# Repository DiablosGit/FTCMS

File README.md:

This is an attempt to build an easy to use BMS on easy to use Hardware. Everyone contributing to this project is welcome.

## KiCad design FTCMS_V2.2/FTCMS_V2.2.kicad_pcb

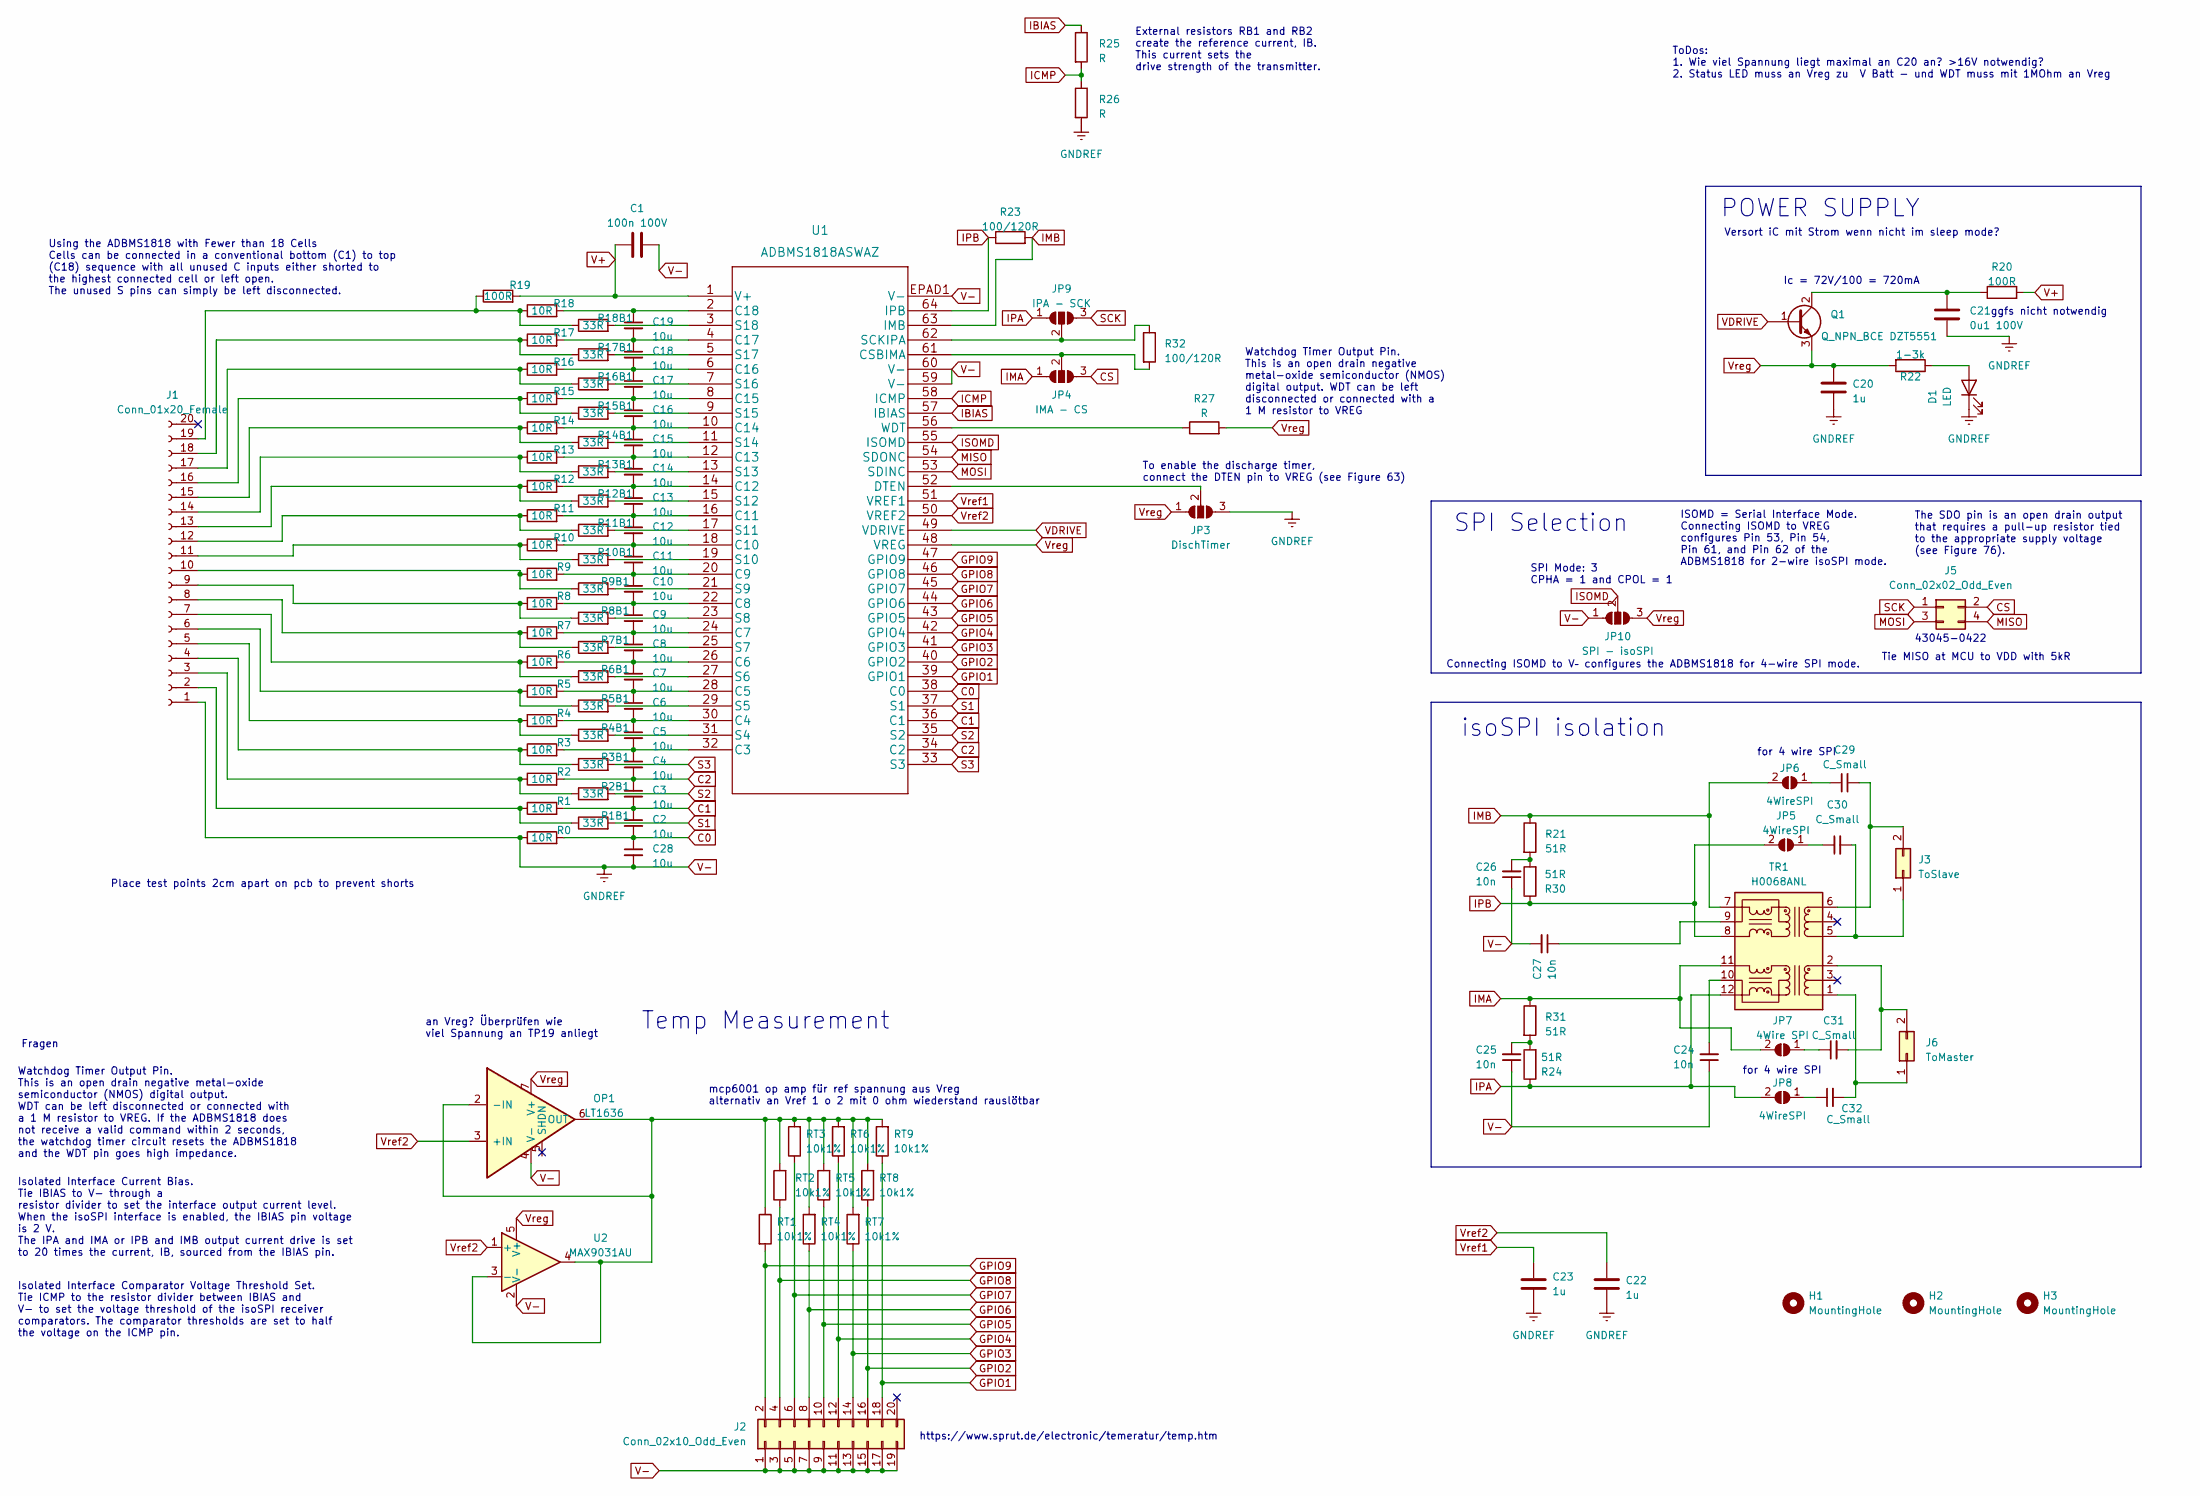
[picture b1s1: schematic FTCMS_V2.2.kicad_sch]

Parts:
C1: 100n 100V; C_1206_3216Metric_Pad1.33x1.80mm_HandSolder
C2, C3, C4, C5, C6, C7, C8, C9, C10, C11, C12, C13, C14, C15, C16, C17, C18, C19, C28: 10u; C_0603_1608Metric_Pad1.08x0.95mm_HandSolder
C20, C22, C23: 1u; C_1206_3216Metric_Pad1.33x1.80mm_HandSolder
C21: 0u1 100V; C_1206_3216Metric_Pad1.33x1.80mm_HandSolder
C24, C25, C26, C27: 10n; C_1206_3216Metric_Pad1.33x1.80mm_HandSolder
C29, C30, C31, C32: C_Small; C_1206_3216Metric_Pad1.33x1.80mm_HandSolder
D1: LED; LED_1206_3216Metric_Pad1.42x1.75mm_HandSolder
H1, H2, H3: MountingHole; MountingHole_3.2mm_M3_DIN965
J1: Conn_01x20_Female; PinSocket_2x10_P2.54mm_Vertical
J2: Conn_02x10_Odd_Even; PinSocket_2x10_P2.54mm_Vertical
J3: ToSlave; Molex_Micro-Fit_3.0_43650-0200_1x02_P3.00mm_Horizontal
J5: Conn_02x02_Odd_Even; Molex_Micro-Fit_3.0_43045-0400_2x02_P3.00mm_Horizontal
J6: ToMaster; Molex_Micro-Fit_3.0_43650-0200_1x02_P3.00mm_Horizontal
JP3: DischTimer; SolderJumper-3_P2.0mm_Open_TrianglePad1.0x1.5mm
JP4: IMA - CS; SolderJumper-3_P2.0mm_Open_TrianglePad1.0x1.5mm
JP5, JP6, JP8: 4WireSPI; SolderJumper-2_P1.3mm_Open_TrianglePad1.0x1.5mm
JP7: 4Wire SPI; SolderJumper-2_P1.3mm_Open_TrianglePad1.0x1.5mm
JP9: IPA - SCK; SolderJumper-3_P2.0mm_Open_TrianglePad1.0x1.5mm
JP10: SPI - isoSPI; SolderJumper-3_P2.0mm_Open_TrianglePad1.0x1.5mm
OP1: LT1636; DIP-8_W7.62mm_Socket_LongPads
Q1: Q_NPN_BCE DZT5551; SOT-223-3_TabPin2
R0, R1, R2, R3, R4, R5, R6, R7, R8, R9, R10, R11, R12, R13, R14, R15, R16, R17, R18: 10R; R_1206_3216Metric_Pad1.30x1.75mm_HandSolder
R1B1, R2B1, R3B1, R4B1, R5B1, R6B1, R7B1, R8B1, R9B1, R10B1, R11B1, R12B1, R13B1, R14B1, R15B1, R16B1, R17B1, R18B1: 33R; R_1206_3216Metric_Pad1.30x1.75mm_HandSolder
R19, R20: 100R; R_1206_3216Metric_Pad1.30x1.75mm_HandSolder
R21, R24, R30, R31: 51R; R_1206_3216Metric_Pad1.30x1.75mm_HandSolder
R22: 1-3k; R_1206_3216Metric_Pad1.30x1.75mm_HandSolder
R23, R32: 100/120R; R_1206_3216Metric_Pad1.30x1.75mm_HandSolder
R25, R26, R27: R; R_1206_3216Metric_Pad1.30x1.75mm_HandSolder
RT1, RT2, RT3, RT4, RT5, RT6, RT7, RT8, RT9: 10k1%; R_1206_3216Metric_Pad1.30x1.75mm_HandSolder
TR1: H0068ANL
U1: ADBMS1818ASWAZ; LQFP-64-1EP_10x10mm_P0.5mm_EP5x5mm_ThermalVias
U2: MAX9031AU; SOT-23-5

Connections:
C0: C2.2, C28.1, R0.2, U1.38 (C0)
C1: C2.1, C3.2, R1.2, U1.36 (C1)
C2: C3.1, C4.2, R2.2, U1.34 (C2)
CS: J5.2, JP4.3 (B)
GPIO1: J2.18, RT9.1, U1.39 (GPIO1)
GPIO2: J2.16, RT8.1, U1.40 (GPIO2)
GPIO3: J2.14, RT7.1, U1.41 (GPIO3)
GPIO4: J2.12, RT6.1, U1.42 (GPIO4)
GPIO5: J2.10, RT5.1, U1.43 (GPIO5)
GPIO6: J2.8, RT4.1, U1.44 (GPIO6)
GPIO7: J2.6, RT3.1, U1.45 (GPIO7)
GPIO8: J2.4, RT2.1, U1.46 (GPIO8)
GPIO9: J2.2, RT1.2, U1.47 (GPIO9)
IBIAS: R25.1, U1.57 (IBIAS)
ICMP: R25.2, R26.1, U1.58 (ICMP)
IMA: JP4.1 (A), JP7.2 (B), R31.1, TR1.11 (RX-)
IMB: JP6.2 (B), R21.1, R23.2, TR1.7 (TX-), U1.63 (IMB)
IPA: JP8.2 (B), JP9.1 (A), R24.1, TR1.12 (RX+)
IPB: JP5.2 (B), R23.1, R30.1, TR1.8 (TX+), U1.64 (IPB)
ISOMD: JP10.2 (C), U1.55 (ISOMD)
MISO: J5.4, U1.54 (SDONC)
MOSI: J5.3, U1.53 (SDINC)
unnamed: C25.2, R24.2, R31.2
unnamed: C26.2, R21.2, R30.2
unnamed: D1.2 (A), R22.1
unnamed: J1.2, R1.1, R1B1.1
unnamed: J1.3, R2.1, R2B1.1
unnamed: J1.4, R3.1, R3B1.1
unnamed: J1.5, R4.1, R4B1.1
unnamed: J1.6, R5.1, R5B1.1
unnamed: J1.7, R6.1, R6B1.1
unnamed: J1.8, R7.1, R7B1.1
unnamed: J1.9, R8.1, R8B1.1
unnamed: J1.10, R9.1, R9B1.1
unnamed: J1.11, R10.1, R10B1.1
unnamed: J1.12, R11.1, R11B1.1
unnamed: J1.13, R12.1, R12B1.1
unnamed: J1.14, R13.1, R13B1.1
unnamed: J1.15, R14.1, R14B1.1
unnamed: J1.16, R15.1, R15B1.1
unnamed: J1.17, R16.1, R16B1.1
unnamed: J1.18, R17.1, R17B1.1
unnamed: J1.19, R18.1, R18B1.1, R19.1
unnamed: C30.2, J3.1, TR1.5 (TD+)
unnamed: C29.2, J3.2, TR1.6 (TD-)
unnamed: C32.2, J6.1, TR1.1 (RD+)
unnamed: C31.2, J6.2, TR1.2 (RD-)
unnamed: JP3.2 (C), U1.52 (DTEN)
unnamed: JP4.2 (C), R32.2, U1.61 (CSBIMA)
unnamed: C30.1, JP5.1 (A)
unnamed: C29.1, JP6.1 (A)
unnamed: C31.1, JP7.1 (A)
unnamed: C32.1, JP8.1 (A)
unnamed: JP9.2 (C), R32.1, U1.62 (SCKIPA)
unnamed: OP1.2 (-IN), OP1.6 (OUT), RT1.1, RT2.2, RT3.2, RT4.2, RT5.2, RT6.2, RT7.2, RT8.2, RT9.2, U2.3 (-), U2.4
unnamed: C21.1, Q1.2 (C), R20.1
unnamed: C24.2, TR1.10 (RXCT)
unnamed: C27.1, TR1.9 (TXCT)
unnamed: C4.1, C5.2, R3.2, U1.32 (C3)
unnamed: C5.1, C6.2, R4.2, U1.30 (C4)
unnamed: C6.1, C7.2, R5.2, U1.28 (C5)
unnamed: C7.1, C8.2, R6.2, U1.26 (C6)
unnamed: C8.1, C9.2, R7.2, U1.24 (C7)
unnamed: C9.1, C10.2, R8.2, U1.22 (C8)
unnamed: C10.1, C11.2, R9.2, U1.20 (C9)
unnamed: C11.1, C12.2, R10.2, U1.18 (C10)
unnamed: C12.1, C13.2, R11.2, U1.16 (C11)
unnamed: C13.1, C14.2, R12.2, U1.14 (C12)
unnamed: C14.1, C15.2, R13.2, U1.12 (C13)
unnamed: C15.1, C16.2, R14.2, U1.10 (C14)
unnamed: C16.1, C17.2, R15.2, U1.8 (C15)
unnamed: C17.1, C18.2, R16.2, U1.6 (C16)
unnamed: C18.1, C19.2, R17.2, U1.4 (C17)
unnamed: C19.1, R18.2, U1.2 (C18)
unnamed: R4B1.2, U1.31 (S4)
unnamed: R5B1.2, U1.29 (S5)
unnamed: R6B1.2, U1.27 (S6)
unnamed: R7B1.2, U1.25 (S7)
unnamed: R8B1.2, U1.23 (S8)
unnamed: R9B1.2, U1.21 (S9)
unnamed: R10B1.2, U1.19 (S10)
unnamed: R11B1.2, U1.17 (S11)
unnamed: R12B1.2, U1.15 (S12)
unnamed: R13B1.2, U1.13 (S13)
unnamed: R14B1.2, U1.11 (S14)
unnamed: R15B1.2, U1.9 (S15)
unnamed: R16B1.2, U1.7 (S16)
unnamed: R17B1.2, U1.5 (S17)
unnamed: R18B1.2, U1.3 (S18)
unnamed: R27.1, U1.56 (WDT)
S1: R1B1.2, U1.37 (S1)
S2: R2B1.2, U1.35 (S2)
S3: R3B1.2, U1.33 (S3)
SCK: J5.1, JP9.3 (B)
V+: C1.1, R19.2, R20.2, U1.1 (V+)
V-: C1.2, C20.2, C21.2, C22.2, C23.2, C24.1, C25.1, C26.1, C27.2, C28.2, D1.1 (K), J1.1, J2.1, J2.3, J2.5, J2.7, J2.9, J2.11, J2.13, J2.15, J2.17, J2.19, JP3.3 (B), JP10.1 (A), R0.1, R26.2, U1.59 (V-), U1.60 (V-), U1.EPAD1 (V-), U2.2 (V-)
VDRIVE: Q1.1 (B), U1.49 (VDRIVE)
Vref1: C23.1, U1.51 (VREF1)
Vref2: C22.1, U1.50 (VREF2), U2.1 (+)
Vreg: C20.1, JP3.1 (A), JP10.3 (B), Q1.3 (E), R22.2, R27.2, U1.48 (VREG), U2.5 (V+)

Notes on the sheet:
ToDos: 1. Wie viel Spannung liegt maximal an C20 an? >16V notwendig? 2. Status LED muss an Vreg zu V Batt - und WDT muss mit 1MOhm an Vreg
https://www.sprut.de/electronic/temeratur/temp.htm
Watchdog Timer Output Pin. This is an open drain negative metal-oxide semiconductor (NMOS) digital output. WDT can be left disconnected or connected with a 1 M resistor to VREG. If the ADBMS1818 does not receive a valid command within 2 seconds, the watchdog timer circuit resets the ADBMS1818 and t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
Watchdog Timer Output Pin. This is an open drain negative metal-oxide semiconductor (NMOS) digital output. WDT can be left disconnected or connected with a 1 M resistor to VREG
SPI Selection
Place test points 2cm apart on pcb to prevent shorts
POWER SUPPLY
To enable the discharge timer, connect the DTEN pin to VREG (see Figure 63)
Temp Measurement
SPI Mode: 3 CPHA = 1 and CPOL = 1
Isolated Interface Current Bias. Tie IBIAS to V- through a resistor divider to set the interface output current level. When the isoSPI interface is enabled, the IBIAS pin voltage is 2 V. The IPA and IMA or IPB and IMB output current drive is set to 20 times the current, IB, sourced from the IBIAS p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
Ic = 72V/100 = 720mA
for 4 wire SPI
isoSPI isolation
an Vreg? Überprüfen wie viel Spannung an TP19 anliegt
43045-0422
mcp6001 op amp für ref spannung aus Vreg alternativ an Vref 1 o 2 mit 0 ohm wiederstand rauslötbar
External resistors RB1 and RB2 create the reference current, IB. This current sets the drive strength of the transmitter.
Using the ADBMS1818 with Fewer than 18 Cells Cells can be connected in a conventional bottom (C1) to top (C18) sequence with all unused C inputs either shorted to the highest connected cell or left open. The unused S pins can simply be left disconnected.
Tie MISO at MCU to VDD with 5kR
ggfs nicht notwendig
Versort iC mit Strom wenn nicht im sleep mode?
Isolated Interface Comparator Voltage Threshold Set. Tie ICMP to the resistor divider between IBIAS and V- to set the voltage threshold of the isoSPI receiver comparators. The comparator thresholds are set to half the voltage on the ICMP pin.
ISOMD = Serial Interface Mode. Connecting ISOMD to VREG configures Pin 53, Pin 54, Pin 61, and Pin 62 of the ADBMS1818 for 2-wire isoSPI mode.
Connecting ISOMD to V– configures the ADBMS1818 for 4-wire SPI mode.
Fragen
The SDO pin is an open drain output that requires a pull-up resistor tied to the appropriate supply voltage (see Figure 76).

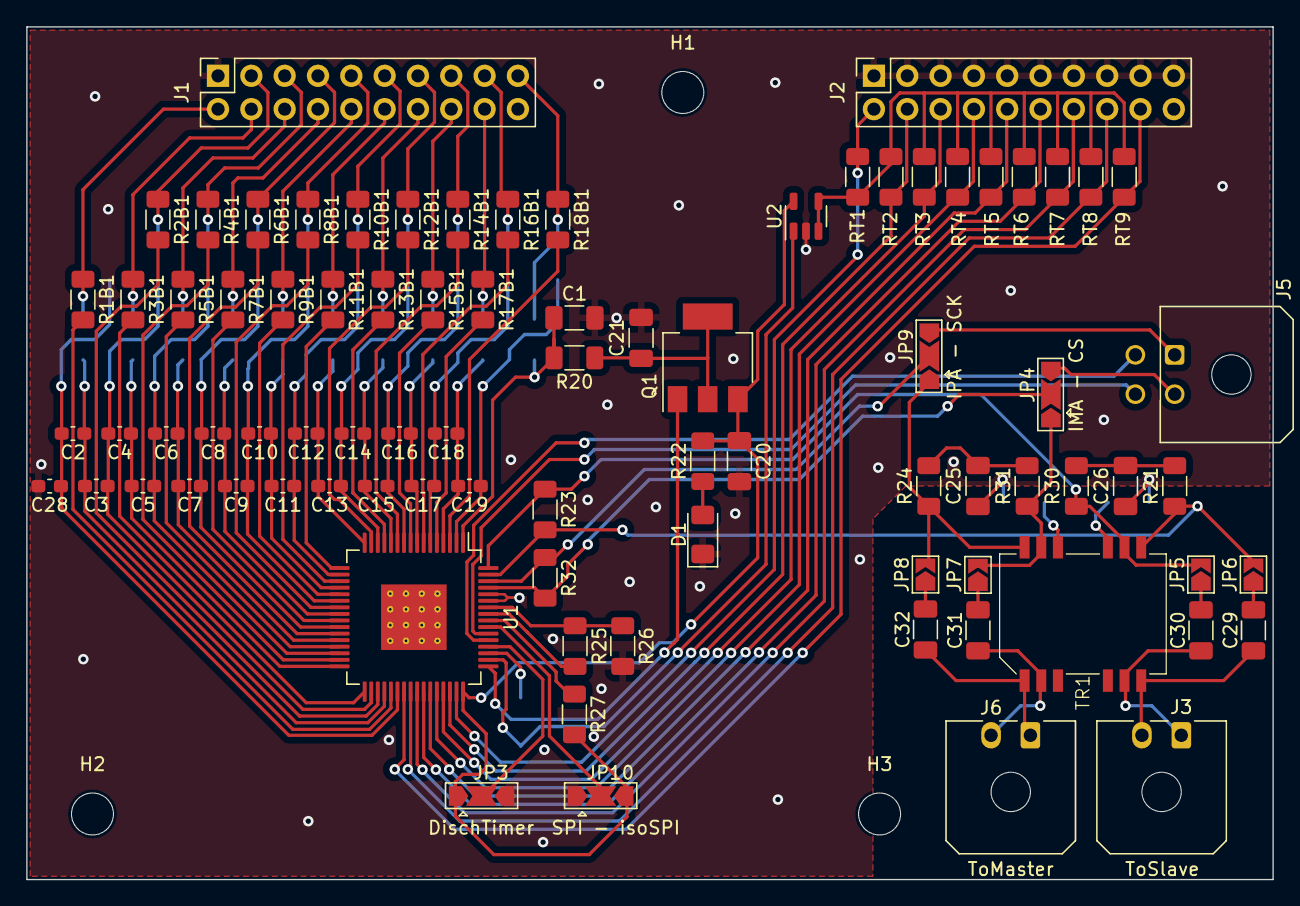
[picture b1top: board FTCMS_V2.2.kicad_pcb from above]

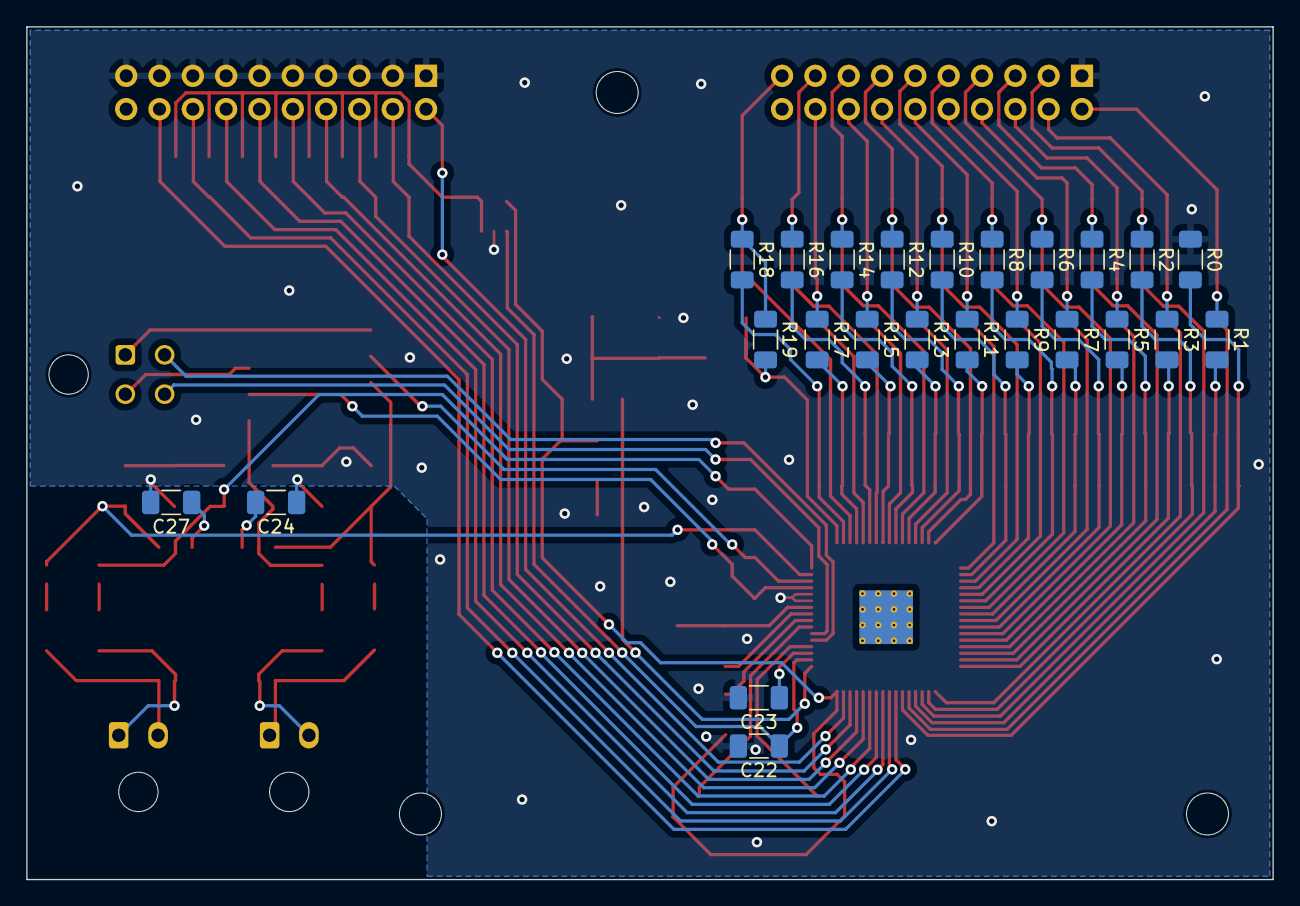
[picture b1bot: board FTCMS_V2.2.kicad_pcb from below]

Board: 2 copper layers, 95.0 x 65.0 mm, 111 parts (24 on the bottom side), 100 nets.

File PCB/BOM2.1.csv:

"ID";"Bezeichner";"Footprint";"Stückzahl";"Bezeichnung";"Anbieter und Referenz";
1;"U1";"LQFP-64-1EP_10x10mm_P0.5mm_EP5x5mm_ThermalVias";1;"ADBMS1818ASWAZ";;;
2;"TR1";"H0068ANL";1;"H0068ANL";;;
3;"TP21,TP20,TP19,TP18,TP17,TP16,TP15,TP14,TP13,TP12,TP11,TP10,TP9,TP8,TP7,TP6,TP5,TP4,TP3,TP2,TP1,TP0";"TestPoint_Pad_D1.0mm";22;"TestPoint";;;
4;"RT9,RT8,RT7,RT6,RT5,RT4,RT3,RT2,RT1";"R_1206_3216Metric_Pad1.30x1.75mm_HandSolder";9;"10k1%";;;
5;"R32,R23";"R_1206_3216Metric_Pad1.30x1.75mm_HandSolder";2;"100/120R";;;
6;"R31,R30,R24,R21";"R_1206_3216Metric_Pad1.30x1.75mm_HandSolder";4;"51R";;;
7;"R27,R26,R25";"R_1206_3216Metric_Pad1.30x1.75mm_HandSolder";3;"R";;;
8;"R22";"R_1206_3216Metric_Pad1.30x1.75mm_HandSolder";1;"1-3k";;;
9;"R20,R19";"R_1206_3216Metric_Pad1.30x1.75mm_HandSolder";2;"100R";;;
10;"R18B1,R17B1,R16B1,R15B1,R14B1,R13B1,R12B1,R11B1,R10B1,R9B1,R8B1,R7B1,R6B1,R5B1,R4B1,R3B1,R2B1,R1B1";"R_1206_3216Metric_Pad1.30x1.75mm_HandSolder";18;"33R";;;
11;"R18,R17,R16,R15,R14,R13,R12,R11,R10,R9,R8,R7,R6,R5,R4,R3,R2,R1,R0";"R_1206_3216Metric_Pad1.30x1.75mm_HandSolder";19;"10R";;;
12;"Q1";"SOT-223-3_TabPin2";1;"Q_NPN_BCE DZT5551";;;
13;"OP1";"DIP-8_W7.62mm_Socket_LongPads";1;"LT1636";;;
14;"JP9,JP4,JP3";"SolderJumper-3_P2.0mm_Open_TrianglePad1.0x1.5mm";3;"SolderJumper_3_Open";;;
15;"JP8,JP7,JP6,JP5";"SolderJumper-2_P1.3mm_Open_TrianglePad1.0x1.5mm";4;"SolderJumper_2_Open";;;
16;"JP2";"SolderJumper-2_P1.3mm_Open_TrianglePad1.0x1.5mm";1;"isoSPI Mode";;;
17;"JP1";"SolderJumper-2_P1.3mm_Open_TrianglePad1.0x1.5mm";1;"SPI Mode";;;
18;"J6";"Molex_Micro-Fit_3.0_43045-0212_2x01_P3.00mm_Vertical";1;"ToMaster";;;
19;"J4";"Molex_Micro-Fit_3.0_43045-0400_2x02_P3.00mm_Horizontal";1;"Conn_02x02_Odd_Even";;;
20;"J3";"Molex_Micro-Fit_3.0_43045-0212_2x01_P3.00mm_Vertical";1;"ToSlave";;;
21;"H3,H2,H1";"MountingHole_3.2mm_M3_DIN965";3;"MountingHole";;;
22;"D1";"LED_1206_3216Metric_Pad1.42x1.75mm_HandSolder";1;"LED";;;
23;"C27,C26,C25,C24";"C_1206_3216Metric_Pad1.33x1.80mm_HandSolder";4;"10n";;;
24;"C23,C20";"C_1206_3216Metric_Pad1.33x1.80mm_HandSolder";2;"1u ";;;
25;"C22";"C_1206_3216Metric_Pad1.33x1.80mm_HandSolder";1;"1u";;;
26;"C21";"C_1206_3216Metric_Pad1.33x1.80mm_HandSolder";1;"0u1 100V";;;
27;"C19,C18,C17,C16,C15,C14,C13,C12,C11,C10,C9,C8,C7,C6,C5,C4,C3,C2";"C_1206_3216Metric_Pad1.33x1.80mm_HandSolder";18;"C_Small";;;
28;"C1";"C_1206_3216Metric_Pad1.33x1.80mm_HandSolder";1;"100n 100V";;;
29;"J2";"Molex_Micro-Fit_3.0_43045-2000_2x10_P3.00mm_Horizontal";1;"Conn_02x10_Odd_Even";;;
30;"J1";"Molex_Micro-Fit_3.0_43045-2000_2x10_P3.00mm_Horizontal";1;"Conn_01x20_Female";;;

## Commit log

2024-07-11 sending bytes via serial and displaying responses
2024-10-03 itroducing second project
2024-10-03 works, currently working on translating the shit..
2024-11-13 completed init function
2024-11-13 finished init function
2025-02-13 seems to work, no more pec error. Used 10k pullup between miso and vdd 5V arduino
2025-02-13 added voltage read and sum of voltage read
2025-02-16 cleanup
2025-03-27 integrated aux measurement routine.. not yet tested
2025-03-27 test
2025-03-27 initial comit to dev_david
2025-03-27 removed kicad project
2025-03-31 Added in main: + case 7: // Start Status ADC Measurement + case 8: // Read Status registers + case 9: // Start Combined Cell Voltage and GPIO1, GPIO2 Conversion and Poll Status + case 11: // Loop Mea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
    in adbms1818_self:
    + functions Start a Status ADC Conversion , Starts cell voltage and GPIO 1 & 2 c
2025-05-23 platine debug 1
2025-05-25 FCTMS rebuild
2025-05-25 3d modelle der molex-stecker hinzugefügt
